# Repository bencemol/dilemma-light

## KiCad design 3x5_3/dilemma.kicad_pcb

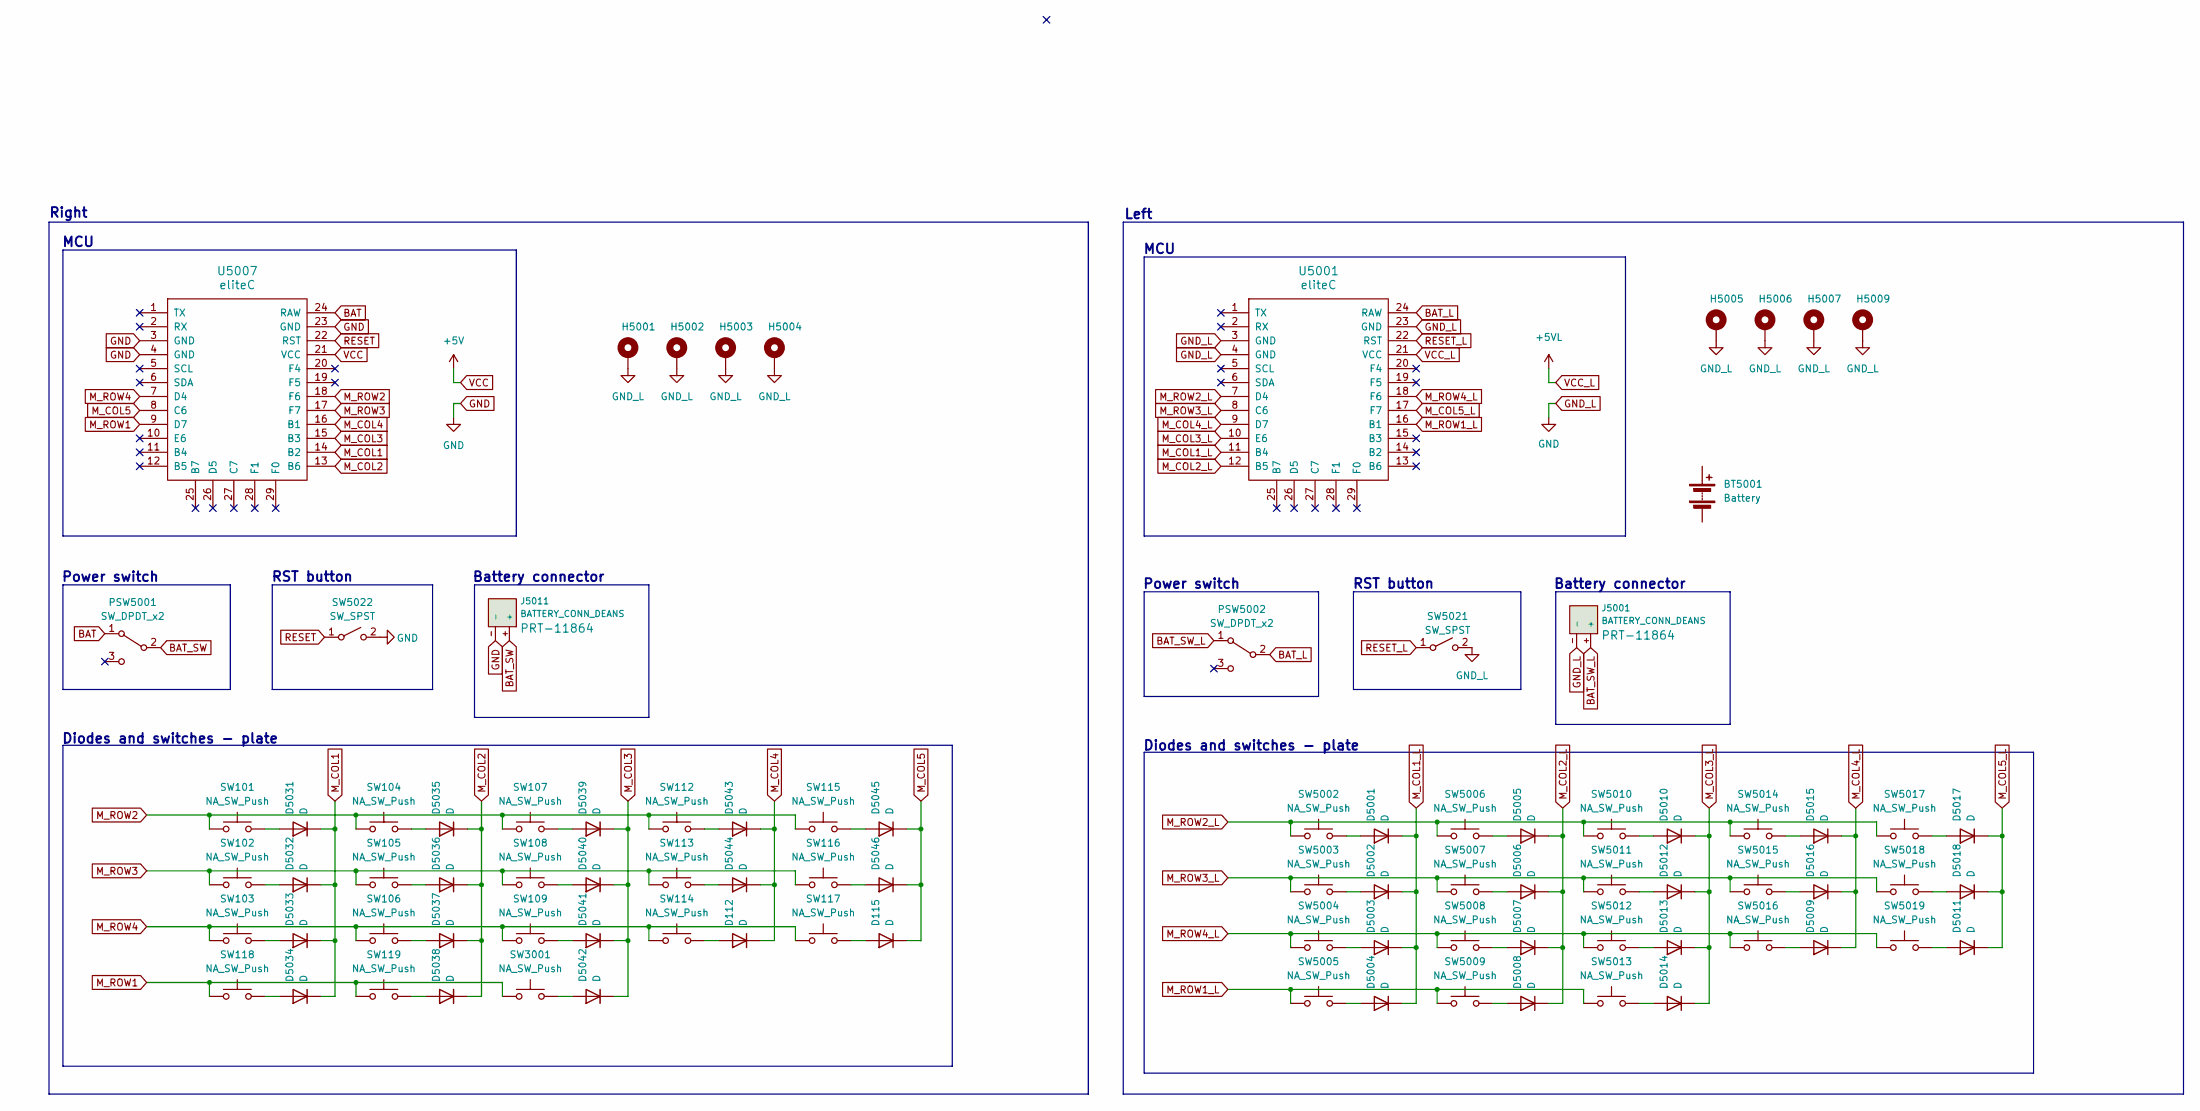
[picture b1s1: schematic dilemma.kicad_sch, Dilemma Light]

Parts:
BT5001: Battery; LP602945-PCM-LD-A14348
D112, D115, D5001, D5002, D5003, D5004, D5005, D5006, D5007, D5008, D5009, D5010, D5011, D5012, D5013, D5014, D5015, D5016, D5017, D5018, D5031, D5032, D5033, D5034, D5035, D5036, D5037, D5038, D5039, D5040, D5041, D5042, D5043, D5044, D5045, D5046: D; D_SOD-123
H5001, H5002, H5003, H5004, H5005, H5006, H5007, H5009: NA_Mount; M2_Mounting_Hole
J5001, J5011: BATTERY_CONN_DEANS; battery_connector_THT
PSW5001, PSW5002: SW_DPDT_x2; Switch_MSK-12C01-07; LCSC C431540
SW101, SW102, SW103, SW104, SW105, SW106, SW107, SW108, SW109, SW112, SW113, SW114, SW115, SW116, SW117, SW118, SW119, SW3001, SW5002, SW5003, SW5004, SW5005, SW5006, SW5007, SW5008, SW5009, SW5010, SW5011, SW5012, SW5013, SW5014, SW5015, SW5016, SW5017, SW5018, SW5019: NA_SW_Push; SW_Kailh_Choc_V1V2_1.00u
SW5021, SW5022: SW_SPST; PushSwitch
U5001, U5007: eliteC; Sparkfun_Pro_Micro

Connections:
BAT: PSW5001.1 (A), U5007.24 (RAW)
BAT_L: PSW5002.2 (B), U5001.24 (RAW)
BAT_SW: J5011.+, PSW5001.2 (B)
BAT_SW_L: J5001.+, PSW5002.1 (A)
GND: H5001.1, H5002.1, H5003.1, H5004.1, H5005.1, H5006.1, H5007.1, H5009.1, J5001.-, J5011.-, SW5021.2 (B), SW5022.2 (B), U5001.3 (GND), U5001.4 (GND), U5001.23 (GND), U5007.3 (GND), U5007.4 (GND), U5007.23 (GND)
M_COL1: D5031.1 (K), D5032.1 (K), D5033.1 (K), D5034.1 (K), U5007.14 (B2)
M_COL1_L: D5001.1 (K), D5002.1 (K), D5003.1 (K), D5004.1 (K), U5001.11 (B4)
M_COL2: D5035.1 (K), D5036.1 (K), D5037.1 (K), D5038.1 (K), U5007.13 (B6)
M_COL2_L: D5005.1 (K), D5006.1 (K), D5007.1 (K), D5008.1 (K), U5001.12 (B5)
M_COL3: D5039.1 (K), D5040.1 (K), D5041.1 (K), D5042.1 (K), U5007.15 (B3)
M_COL3_L: D5010.1 (K), D5012.1 (K), D5013.1 (K), D5014.1 (K), U5001.10 (E6)
M_COL4: D112.1 (K), D5043.1 (K), D5044.1 (K), U5007.16 (B1)
M_COL4_L: D5009.1 (K), D5015.1 (K), D5016.1 (K), U5001.9 (D7)
M_COL5: D115.1 (K), D5045.1 (K), D5046.1 (K), U5007.8 (C6)
M_COL5_L: D5011.1 (K), D5017.1 (K), D5018.1 (K), U5001.17 (F7)
M_ROW1: SW118.1, SW119.1, SW3001.1, U5007.9 (D7)
M_ROW1_L: SW5005.1, SW5009.1, SW5013.1, U5001.16 (B1)
M_ROW2: SW101.1, SW104.1, SW107.1, SW112.1, SW115.1, U5007.18 (F6)
M_ROW2_L: SW5002.1, SW5006.1, SW5010.1, SW5014.1, SW5017.1, U5001.7 (D4)
M_ROW3: SW102.1, SW105.1, SW108.1, SW113.1, SW116.1, U5007.17 (F7)
M_ROW3_L: SW5003.1, SW5007.1, SW5011.1, SW5015.1, SW5018.1, U5001.8 (C6)
M_ROW4: SW103.1, SW106.1, SW109.1, SW114.1, SW117.1, U5007.7 (D4)
M_ROW4_L: SW5004.1, SW5008.1, SW5012.1, SW5016.1, SW5019.1, U5001.18 (F6)
unnamed: D112.2 (A), SW114.2
unnamed: D115.2 (A), SW117.2
unnamed: D5001.2 (A), SW5002.2
unnamed: D5002.2 (A), SW5003.2
unnamed: D5003.2 (A), SW5004.2
unnamed: D5004.2 (A), SW5005.2
unnamed: D5005.2 (A), SW5006.2
unnamed: D5006.2 (A), SW5007.2
unnamed: D5007.2 (A), SW5008.2
unnamed: D5008.2 (A), SW5009.2
unnamed: D5009.2 (A), SW5016.2
unnamed: D5010.2 (A), SW5010.2
unnamed: D5011.2 (A), SW5019.2
unnamed: D5012.2 (A), SW5011.2
unnamed: D5013.2 (A), SW5012.2
unnamed: D5014.2 (A), SW5013.2
unnamed: D5015.2 (A), SW5014.2
unnamed: D5016.2 (A), SW5015.2
unnamed: D5017.2 (A), SW5017.2
unnamed: D5018.2 (A), SW5018.2
unnamed: D5031.2 (A), SW101.2
unnamed: D5032.2 (A), SW102.2
unnamed: D5033.2 (A), SW103.2
unnamed: D5034.2 (A), SW118.2
unnamed: D5035.2 (A), SW104.2
unnamed: D5036.2 (A), SW105.2
unnamed: D5037.2 (A), SW106.2
unnamed: D5038.2 (A), SW119.2
unnamed: D5039.2 (A), SW107.2
unnamed: D5040.2 (A), SW108.2
unnamed: D5041.2 (A), SW109.2
unnamed: D5042.2 (A), SW3001.2
unnamed: D5043.2 (A), SW112.2
unnamed: D5044.2 (A), SW113.2
unnamed: D5045.2 (A), SW115.2
unnamed: D5046.2 (A), SW116.2
RESET: SW5022.1 (A), U5007.22 (RST)
RESET_L: SW5021.1 (A), U5001.22 (RST)
VCC: U5007.21 (VCC)
VCC_L: U5001.21 (VCC)

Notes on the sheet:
Right
MCU
Power switch
Battery connector
RST button
Left
Diodes and switches - plate

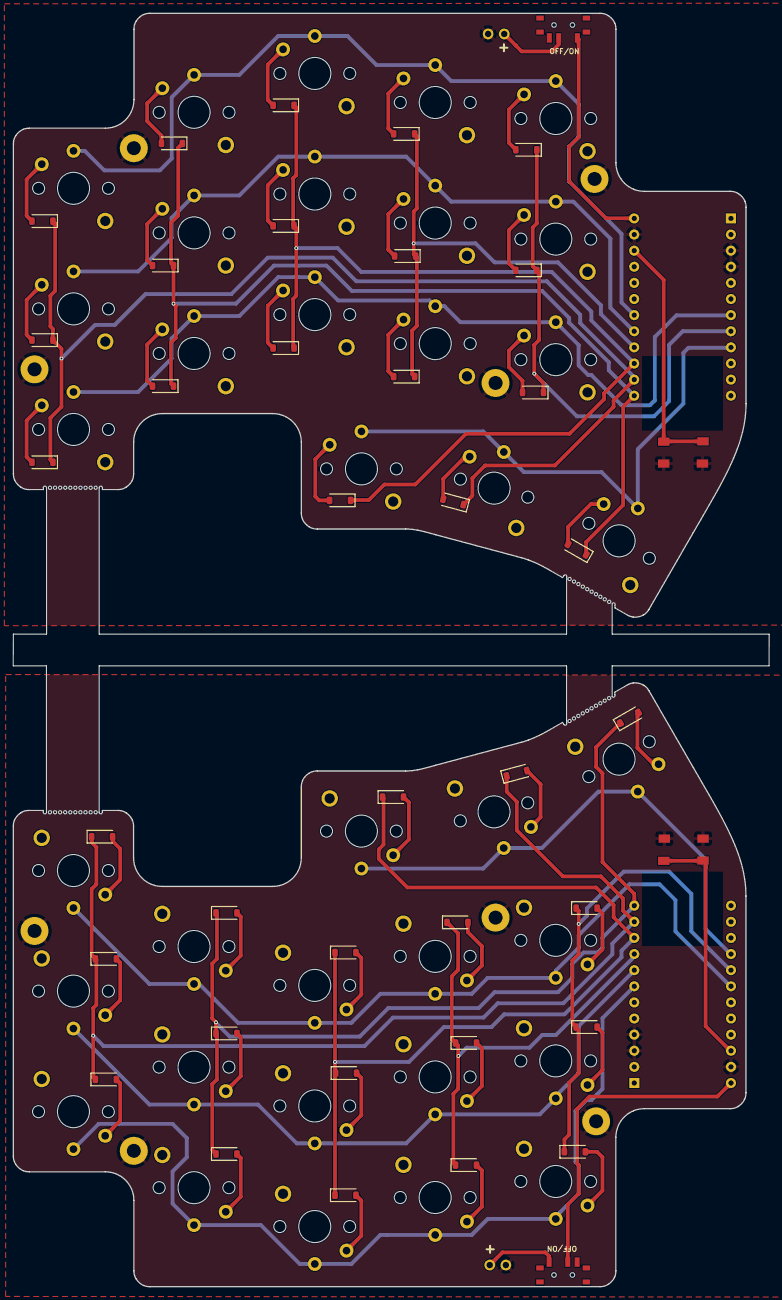
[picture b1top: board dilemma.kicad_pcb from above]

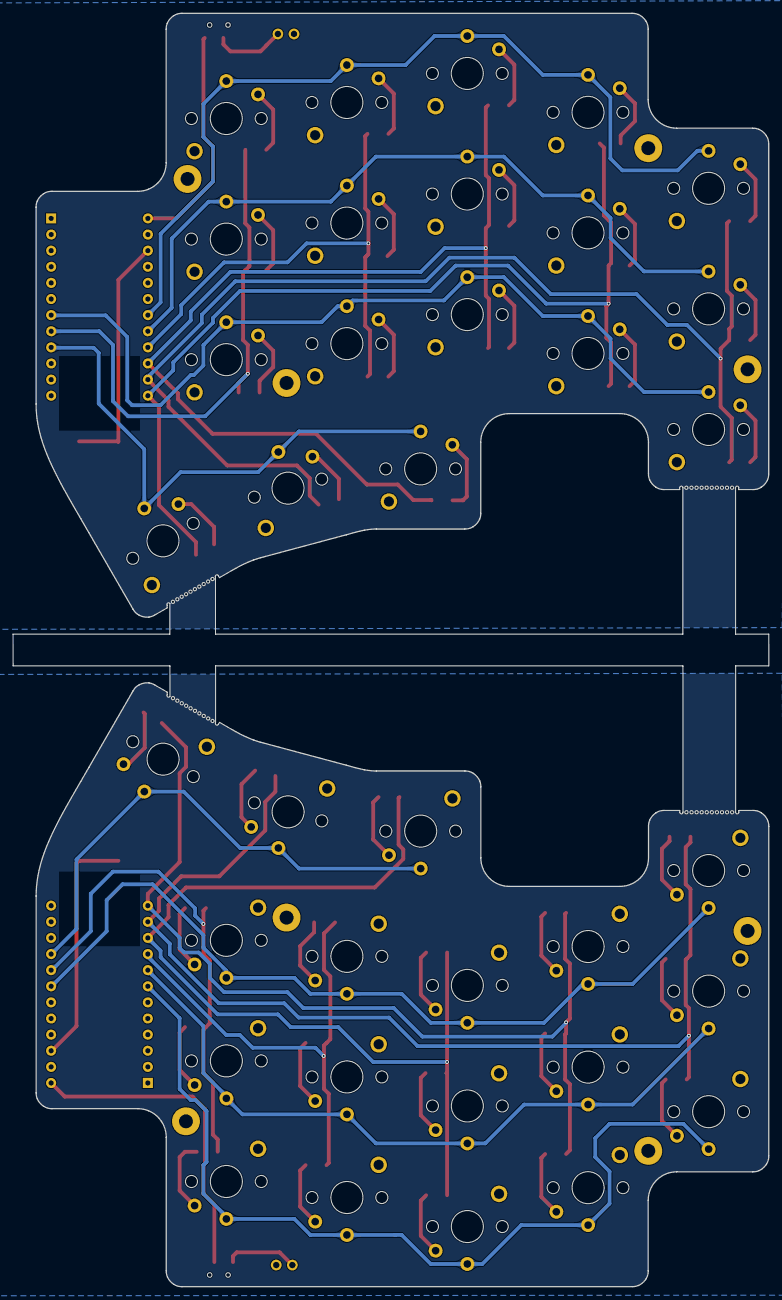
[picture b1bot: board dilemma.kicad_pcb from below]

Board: 2 copper layers, 119.1 x 200.7 mm, 88 parts (39 on the bottom side), 61 nets.

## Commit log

2024-05-20 3x5_3 right side layout
2024-05-20 adjust diode clearance
2024-05-20 left side schematic
2024-05-20 cleanup up left layout
2024-05-20 right side component placement
2024-05-20 right side layout
2024-05-21 cleanup silkscreen
2024-05-26 adjusted layout for case clearance
2024-05-27 add svgs
2024-05-27 solid infill & teardrops
2024-05-27 thicker traces
2024-06-14 fix jst clearance
2024-06-14 choc v1
2024-06-14 choc v2
2024-06-18 right gerber
2024-06-18 left gerber
2024-07-02 switchplate
2024-07-02 add puck screw cutouts
2024-07-02 fix silkscreen
2024-08-17 antenna cutout
2024-08-20 convert to reversible pcb
2024-08-20 refill zones
2024-09-13 add right side edge cuts
2024-09-13 left half edge cuts
2024-09-13 routed right matrix
2024-09-14 routed left matrix
2024-09-15 add right mounting holes
2024-09-15 fix lower right mounting hole
2024-09-17 adjust edge cuts
2024-09-17 reroute
2024-09-21 finish layout
2024-09-22 case clearance & plate
2024-10-09 adjust nicenano .gitignore & fix on/off silkscreen

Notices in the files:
3x5_3/dilemma.kicad_sch:
Licensed under CERN-OHL-W v2
